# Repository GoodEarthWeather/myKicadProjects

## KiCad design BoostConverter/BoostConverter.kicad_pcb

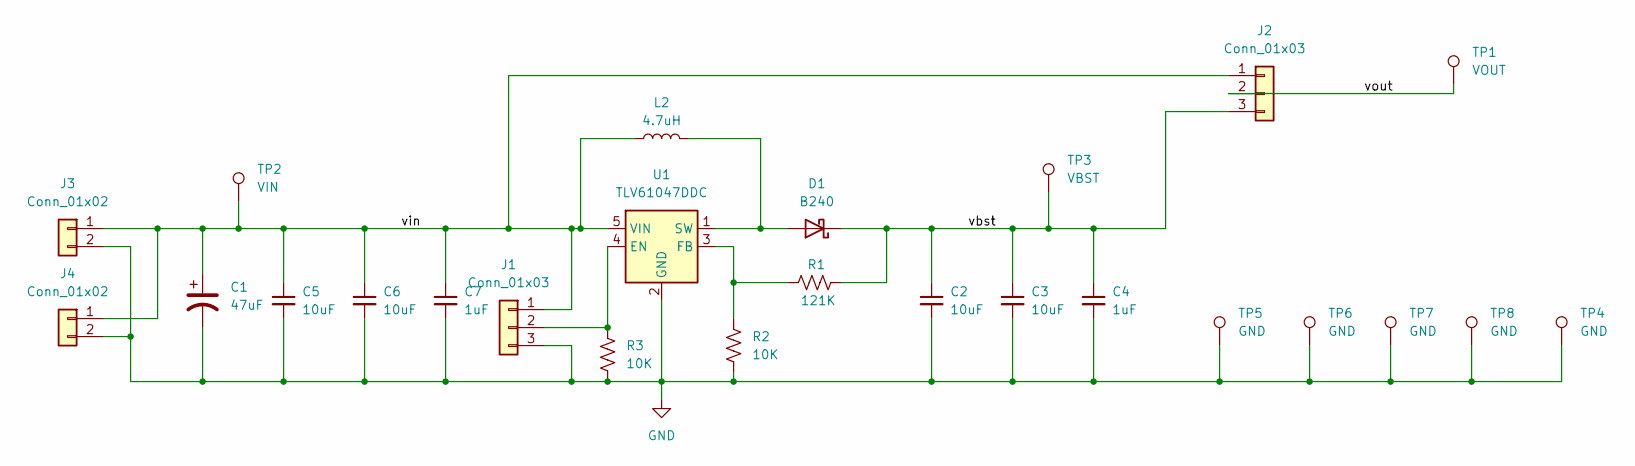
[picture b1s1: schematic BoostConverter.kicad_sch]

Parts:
C1: 47uF; CP_Elec_6.3x5.8; MouserPN 667-EEE-FK1V470P
C2, C3, C5, C6: 10uF; C_1206_3216Metric_Pad1.33x1.80mm_HandSolder; MouserPN 810-CGA5L1X7R1H106K1
C4, C7: 1uF; C_0603_1608Metric_Pad1.08x0.95mm_HandSolder; MouserPN 963-BASG168AB7105KT
D1: B240; D_SMB; MouserPN 625-B240A-E3
J1, J2: Conn_01x03; PinHeader_1x03_P2.54mm_Vertical
J3, J4: Conn_01x02; PinHeader_1x02_P2.54mm_Vertical
L2: 4.7uH; L_Coilcraft_XAL4030-XXX
R1: 121K; R_0603_1608Metric_Pad0.98x0.95mm_HandSolder
R2, R3: 10K; R_0603_1608Metric_Pad0.98x0.95mm_HandSolder
TP1: VOUT; TestPoint_Keystone_5000-5004_Miniature; MouserPN 534-5003
TP2: VIN; TestPoint_Keystone_5000-5004_Miniature; MouserPN 534-5003
TP3: VBST; TestPoint_Keystone_5000-5004_Miniature; MouserPN 534-5003
TP4, TP5, TP6, TP7, TP8: GND; TestPoint_Keystone_5000-5004_Miniature; MouserPN 534-5003
U1: TLV61047DDC; SOT-23-5

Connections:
/vbst: C2.1, C3.1, C4.1, D1.1 (K), J2.3, R1.2, TP3.1
/vin: C1.1, C5.1, C6.1, C7.1, J1.1, J2.1, J3.1, J4.1, L2.1, TP2.1, U1.5 (VIN)
/vout: J2.2, TP1.1
GND: C1.2, C2.2, C3.2, C4.2, C5.2, C6.2, C7.2, J1.3, J3.2, J4.2, R2.2, R3.2, TP4.1, TP5.1, TP6.1, TP7.1, TP8.1, U1.2 (GND)
unnamed: D1.2 (A), L2.2, U1.1 (SW)
unnamed: J1.2, R3.1, U1.4 (EN)
unnamed: R1.1, R2.1, U1.3 (FB)

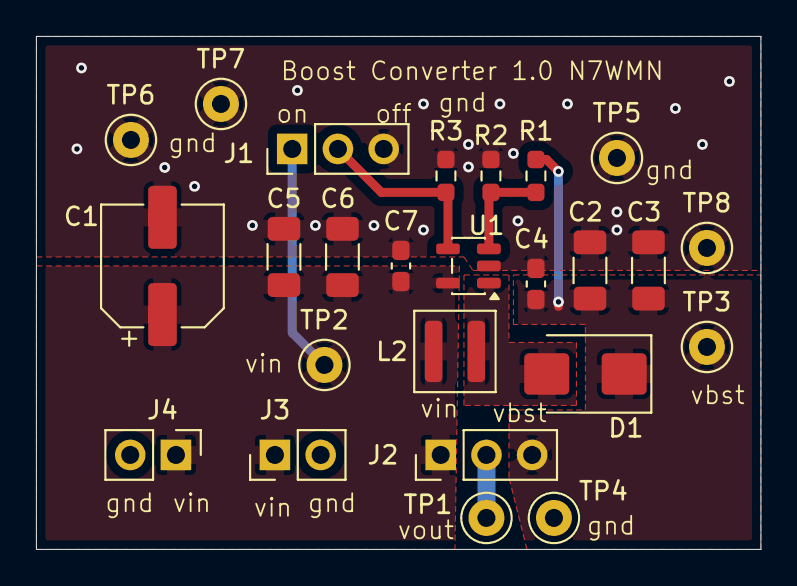
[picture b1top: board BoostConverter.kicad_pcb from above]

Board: 2 copper layers, 40.2 x 28.5 mm, 25 parts (0 on the bottom side), 7 nets.

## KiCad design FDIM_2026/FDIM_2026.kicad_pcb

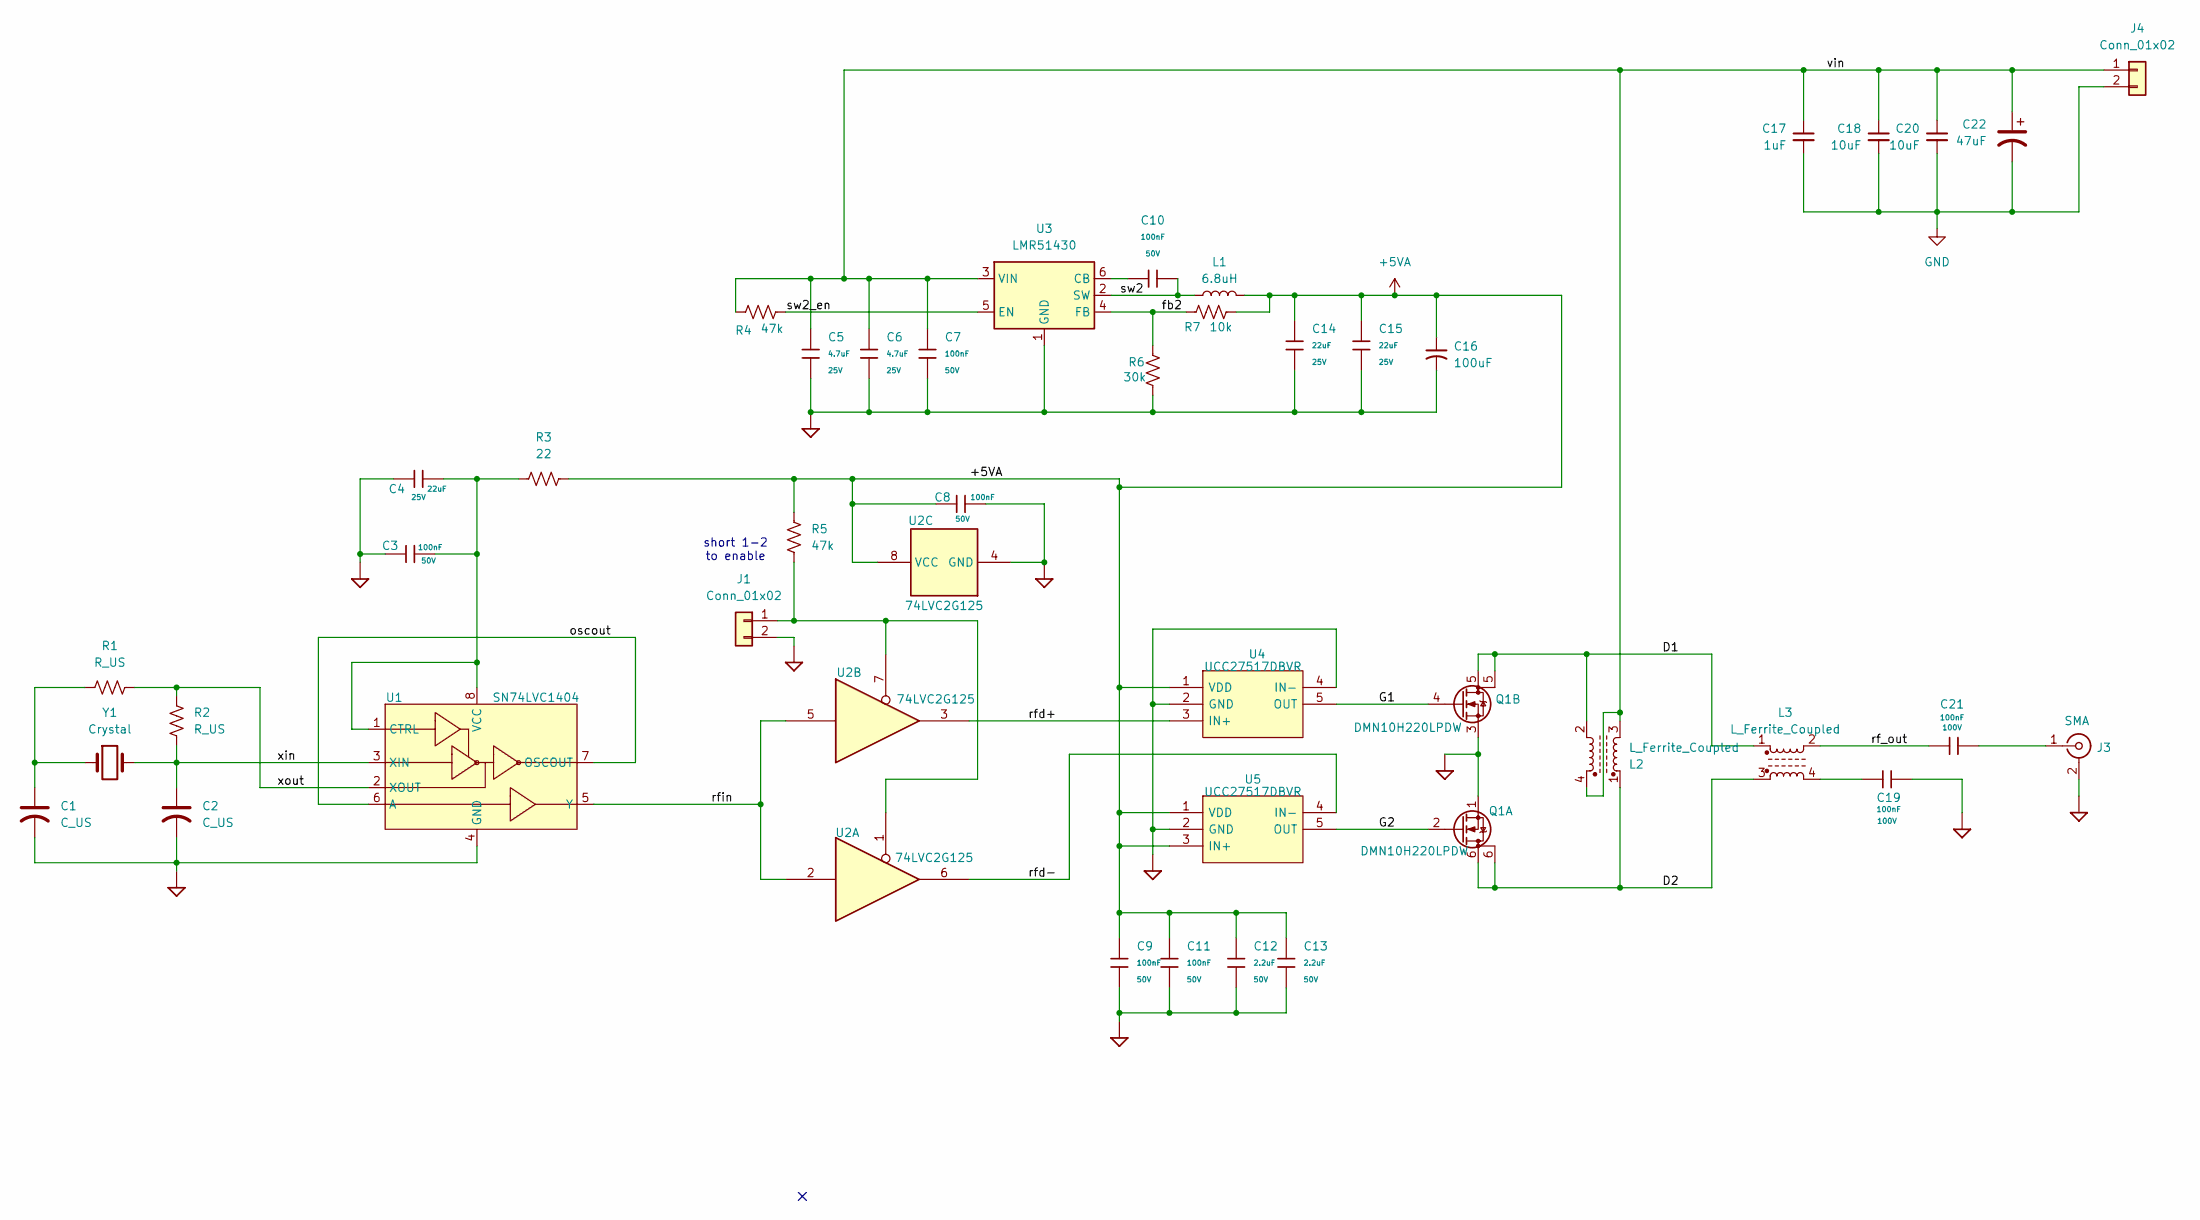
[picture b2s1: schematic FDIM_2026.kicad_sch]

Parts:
C1, C2: C_US; C_0603_1608Metric_Pad1.08x0.95mm_HandSolder
C3, C7, C8, C9, C10, C11: 100nF; C_0603; Voltage Rated 50V; Tolerance ±10%; Part CC0603KRX7R9BB104; LCSC C14663
C4, C14, C15: 22uF; C_0805; Voltage Rated 25V; Tolerance ±20%; Part CL21A226MAQNNNE; LCSC C45783
C5, C6: 4.7uF; C_0805; Voltage Rated 25V; Tolerance ±10%; Part CL21A475KAQNNNE; LCSC C1779
C12, C13: 2.2uF; C_0805; Voltage Rated 50V; Tolerance ±10%; Part CL21A225KBQNNNE; LCSC C377773
C16: 100uF; C_Elec_6.3x5.8; MouserPN 667-EEE-FT1V101AP
C17: 1uF; C_0603; MouserPN 963-BASG168AB7105KT
C18, C20: 10uF; C_1206; MouserPN 810-CGA5L1X7R1H106K1
C19, C21: 100nF; C_0805; Voltage Rated 100V; Tolerance ±10%; Part CL21B104KCFNNNE; LCSC C28233
C22: 47uF; CP_Elec_6.3x5.8; MouserPN 667-EEE-FK1V470P
J1, J4: Conn_01x02; PinHeader_1x02_P2.54mm_Vertical
J3: SMA; SMA_Molex_73251-1153_EdgeMount_Horizontal
L1: 6.8uH; L_TechFuse_SL0624; MouserPN 871-B82472G4682M
L2, L3: L_Ferrite_Coupled; Transformer_Toroid_Horizontal_D14.0mm_Amidon-T50
Q1: DMN10H220LPDW; DMN10H220LPDW13; MouserPN 621-DMN10H220LPDW-13
R1, R2: R_US; R_0603_1608Metric_Pad0.98x0.95mm_HandSolder
R3: 22; R_0603_1608Metric_Pad0.98x0.95mm_HandSolder
R4, R5: 47k; R_0603_1608Metric_Pad0.98x0.95mm_HandSolder
R6: 30k; R_0603_1608Metric_Pad0.98x0.95mm_HandSolder
R7: 10k; R_0603_1608Metric_Pad0.98x0.95mm_HandSolder
U1: SN74LVC1404; TSSOP-8_3x3mm_P0.65mm; MouserPN 595-SN74LVC1404DCTR
U2: 74LVC2G125; SSOP-8_2.95x2.8mm_P0.65mm; MouserPN 595-74LVC2G125DCTRE4
U3: LMR51430; SOT-23-6; LCSC C5185863
U4, U5: UCC27517DBVR; SOT-23-5_HandSoldering; Mouser Part Number 595-UCC27517DBVR
Y1: Crystal; Crystal_HC49-U_Vertical; MouserPN 449-LFXTAL011525BULK

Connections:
+5VA: C8.1, C9.1, C11.1, C12.1, C13.1, C14.1, C15.1, C16.1, L1.2, R3.1, R5.2, R7.1, U2.8 (VCC), U4.1 (VDD), U5.1 (VDD), U5.3 (IN+)
/D1: L2.2, L3.1, Q1.5 (D)
/D2: L2.1, L3.3, Q1.6 (D)
/G1: Q1.4 (G), U4.5 (OUT)
/G2: Q1.2 (G), U5.5 (OUT)
/fb2: R6.2, R7.2, U3.4 (FB)
/oscout: U1.6 (A), U1.7 (OSCOUT)
/rf_out: C21.1, L3.2
/rfd+: U2.3, U4.3 (IN+)
/rfd-: U2.6, U5.4 (IN-)
/rfin: U1.5 (Y), U2.2, U2.5
/sw2: C10.2, L1.1, U3.2 (SW)
/sw2_en: R4.1, U3.5 (EN)
/vin: C5.1, C6.1, C7.1, C17.1, C18.1, C20.1, C22.1, J4.1, L2.3, L2.4, R4.2, U3.3 (VIN)
/xin: C2.1, R2.1, U1.3 (XIN), Y1.2
/xout: R1.2, R2.2, U1.2 (XOUT)
GND: C1.2, C2.2, C3.1, C4.1, C5.2, C6.2, C7.2, C8.2, C9.2, C11.2, C12.2, C13.2, C14.2, C15.2, C16.2, C17.2, C18.2, C19.2, C20.2, C22.2, J1.2, J3.2 (Ext), J4.2, Q1.1 (S), Q1.3 (S), R6.1, U1.4 (GND), U2.4 (GND), U3.1 (GND), U4.2 (GND), U4.4 (IN-), U5.2 (GND)
unnamed: C1.1, R1.1, Y1.1
unnamed: C19.1, L3.4
unnamed: J1.1, R5.1, U2.1, U2.7
unnamed: C21.2, J3.1 (In)
unnamed: C3.2, C4.2, R3.2, U1.1 (CTRL), U1.8 (VCC)
unnamed: C10.1, U3.6 (CB)

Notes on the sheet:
short 1-2 to enable

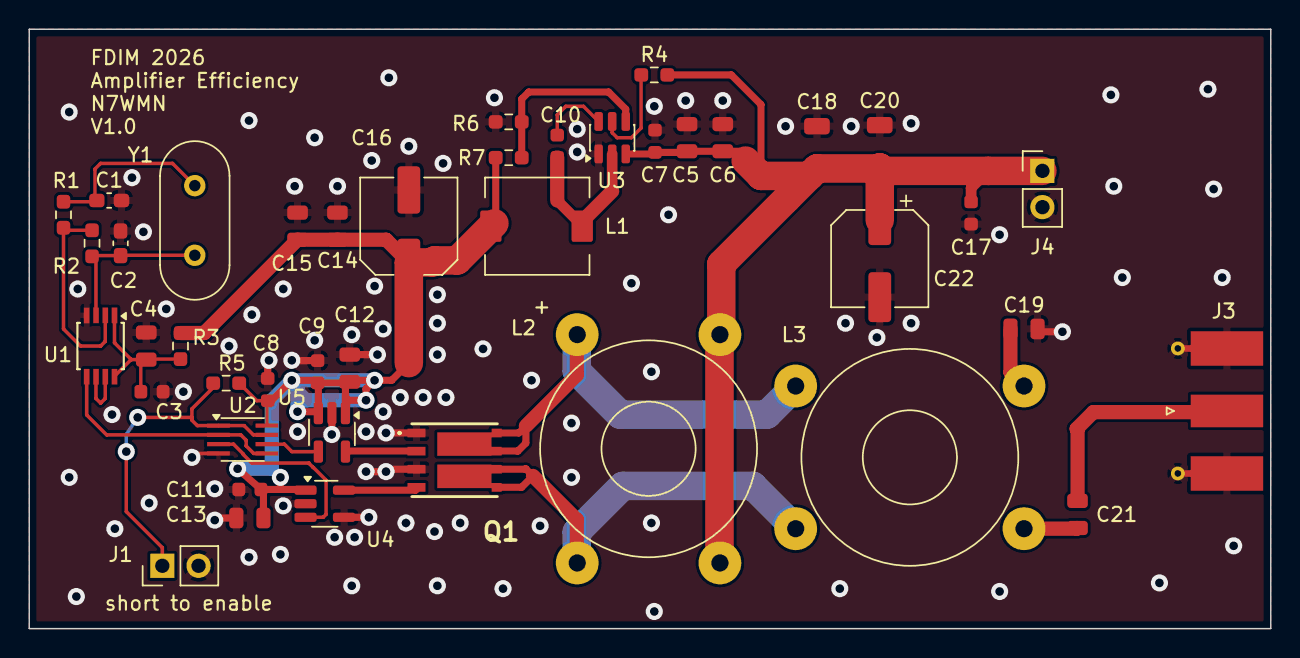
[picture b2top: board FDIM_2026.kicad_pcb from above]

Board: 2 copper layers, 87.0 x 42.0 mm, 42 parts (0 on the bottom side), 23 nets.

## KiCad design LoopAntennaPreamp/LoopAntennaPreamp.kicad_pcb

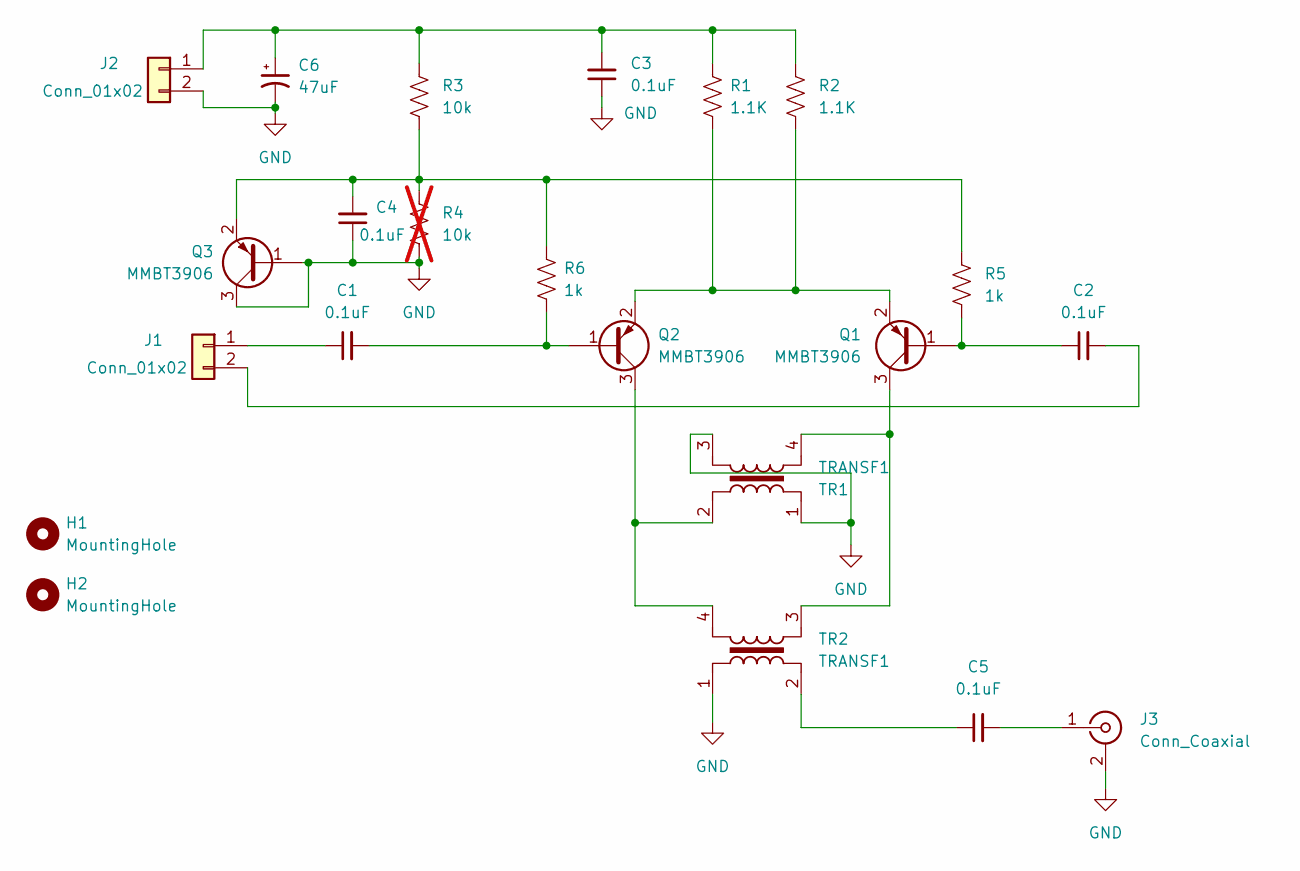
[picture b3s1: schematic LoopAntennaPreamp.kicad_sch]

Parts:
C1, C2, C3, C4, C5: 0.1uF; C_0603_1608Metric_Pad1.08x0.95mm_HandSolder
C6: 47uF; CP_Radial_D5.0mm_P2.50mm
H1, H2: MountingHole; MountingHole_3.2mm_M3_DIN965
J1, J2: Conn_01x02; PinHeader_1x02_P2.54mm_Vertical
J3: Conn_Coaxial; SMA_Amphenol_132289_EdgeMount
Q1, Q2, Q3: MMBT3906; SOT-23_Handsoldering
R1, R2: 1.1K; R_0603_1608Metric_Pad0.98x0.95mm_HandSolder
R3: 10k; R_0603_1608Metric_Pad0.98x0.95mm_HandSolder
R4: 10k; R_0603_1608Metric_Pad0.98x0.95mm_HandSolder; not fitted
R5, R6: 1k; R_0603_1608Metric_Pad0.98x0.95mm_HandSolder
TR1, TR2: TRANSF1; Transformer_Toroid_Horizontal_D10.5mm_Amidon-T37

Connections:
GND: C3.1, C4.1, C6.2, J2.2, J3.2 (Ext), Q3.1 (B), Q3.3 (C), R4.2, TR1.1, TR1.3, TR2.1
unnamed: C5.1, TR2.2
unnamed: C1.1, J1.1
unnamed: C2.2, J1.2
unnamed: C3.2, C6.1, J2.1, R1.1, R2.1, R3.1
unnamed: C5.2, J3.1 (In)
unnamed: C2.1, Q1.1 (B), R5.1
unnamed: Q1.3 (C), TR1.4, TR2.3
unnamed: Q1.2 (E), Q2.2 (E), R1.2, R2.2
unnamed: C1.2, Q2.1 (B), R6.1
unnamed: Q2.3 (C), TR1.2, TR2.4
unnamed: C4.2, Q3.2 (E), R3.2, R4.1, R5.2, R6.2

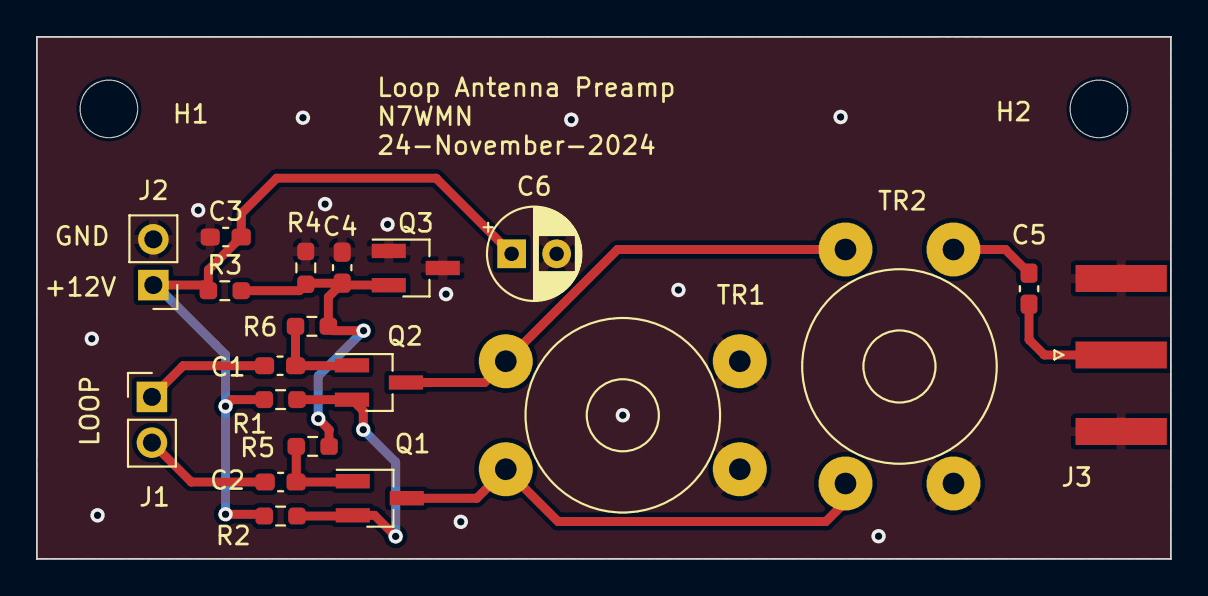
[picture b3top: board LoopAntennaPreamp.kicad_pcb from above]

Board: 2 copper layers, 63.0 x 29.0 mm, 22 parts (0 on the bottom side), 12 nets.

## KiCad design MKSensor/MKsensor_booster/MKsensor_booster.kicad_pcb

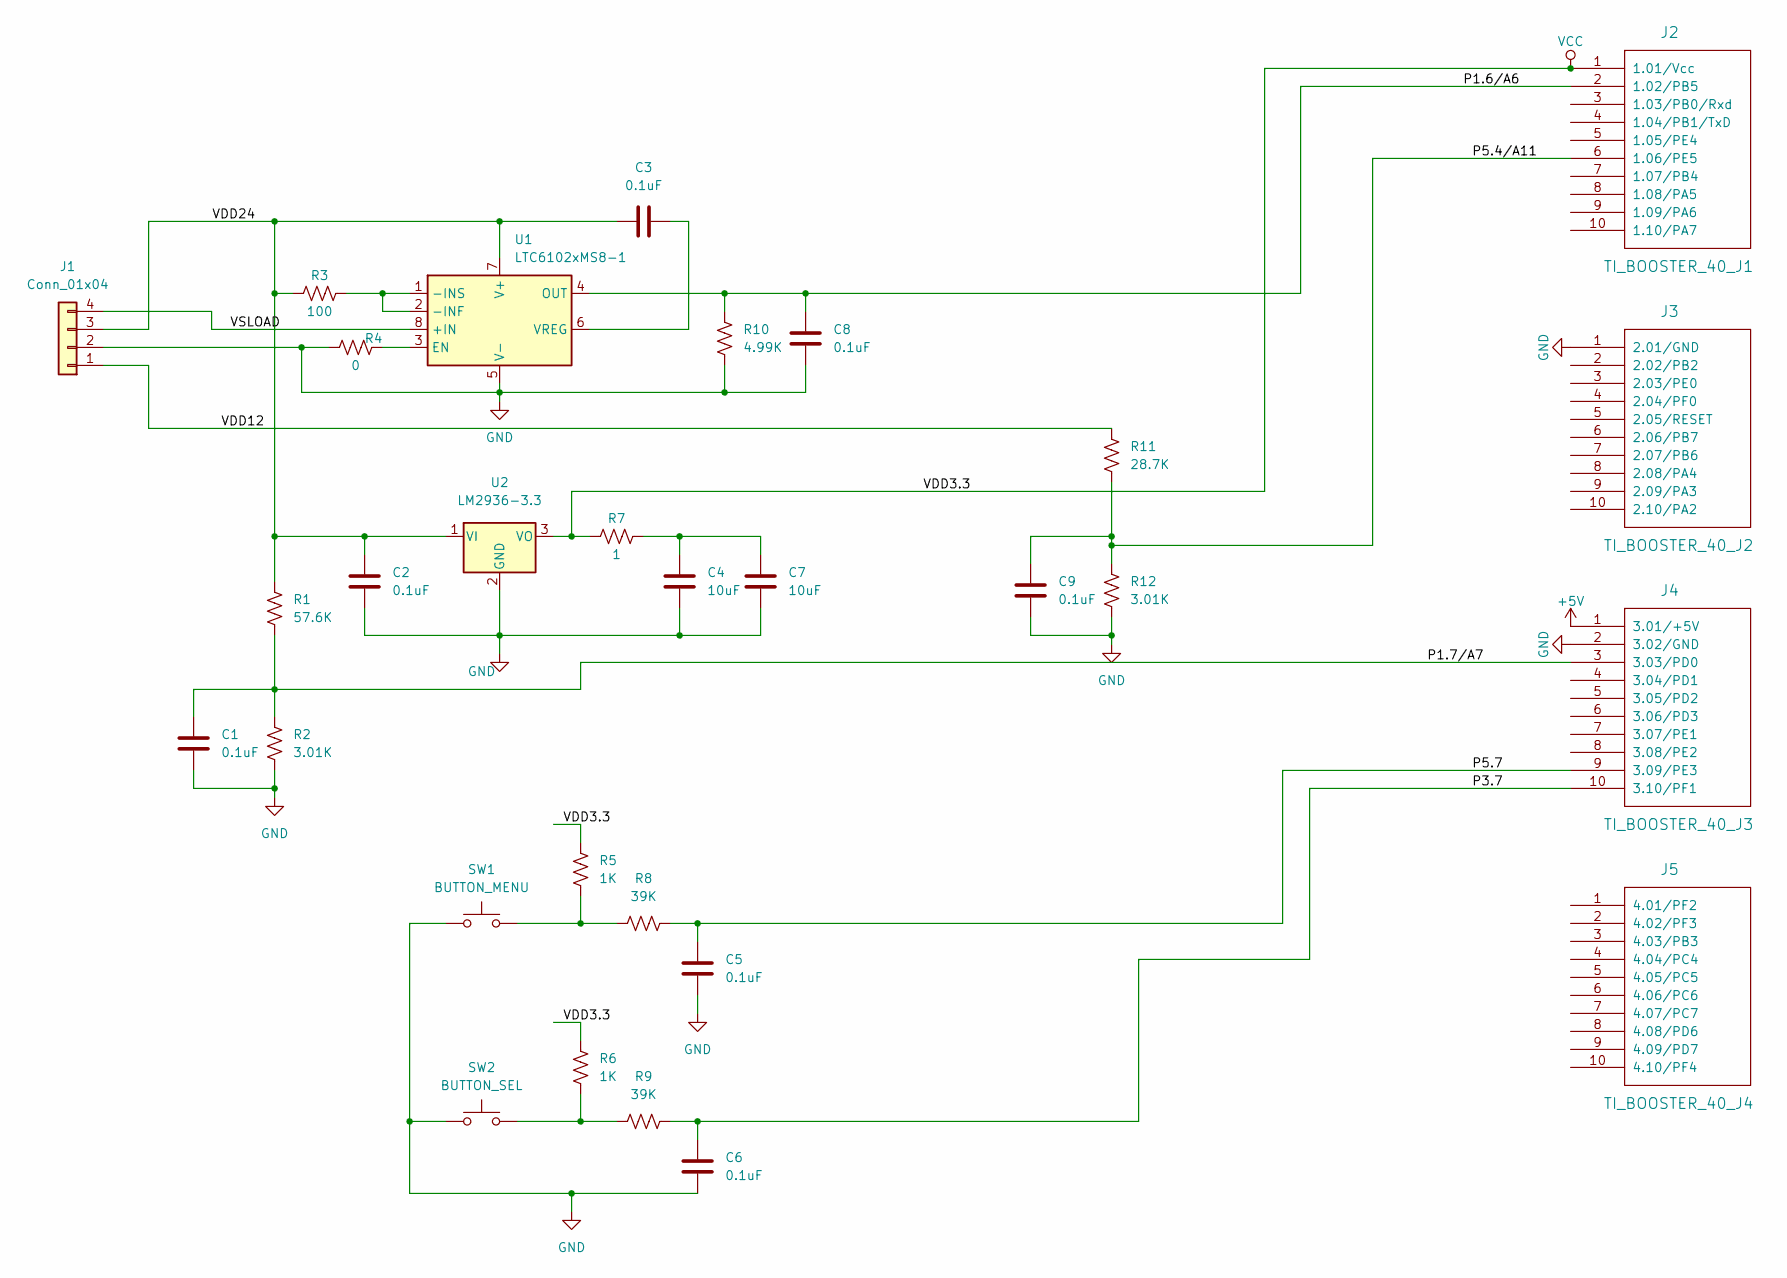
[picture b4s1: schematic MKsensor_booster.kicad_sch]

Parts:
C1, C2, C3, C5, C6, C8, C9: 0.1uF; C_0603_1608Metric_Pad1.08x0.95mm_HandSolder
C4, C7: 10uF; C_0805_2012Metric_Pad1.18x1.45mm_HandSolder
J1: Conn_01x04; PhoenixContact_MCV_1,5_4-G-3.81_1x04_P3.81mm_Vertical
J2: TI_BOOSTER_40_J1; PinHeader_1x10_P2.54mm_Vertical
J3: TI_BOOSTER_40_J2; PinHeader_1x10_P2.54mm_Vertical
J4: TI_BOOSTER_40_J3; PinHeader_1x10_P2.54mm_Vertical
J5: TI_BOOSTER_40_J4; PinHeader_1x10_P2.54mm_Vertical
R1: 57.6K; R_0603_1608Metric_Pad0.98x0.95mm_HandSolder
R2, R12: 3.01K; R_0603_1608Metric_Pad0.98x0.95mm_HandSolder
R3: 100; R_0603_1608Metric_Pad0.98x0.95mm_HandSolder
R4: 0; R_0603_1608Metric_Pad0.98x0.95mm_HandSolder
R5, R6: 1K; R_0603_1608Metric_Pad0.98x0.95mm_HandSolder
R7: 1; R_0603_1608Metric_Pad0.98x0.95mm_HandSolder
R8, R9: 39K; R_0603_1608Metric_Pad0.98x0.95mm_HandSolder
R10: 4.99K; R_0603_1608Metric_Pad0.98x0.95mm_HandSolder
R11: 28.7K; R_0603_1608Metric_Pad0.98x0.95mm_HandSolder
SW1: BUTTON_MENU; SW_SPST_EVQQ2
SW2: BUTTON_SEL; SW_SPST_EVQQ2
U1: LTC6102xMS8-1; MSOP-8_3x3mm_P0.65mm
U2: LM2936-3.3; SOT-223

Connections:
+5V: J4.1 (3.01/+5V)
/P1.6/A6: C8.2, J2.2 (1.02/PB5), R10.1, U1.4 (OUT)
/P1.7/A7: C1.2, J4.3 (3.03/PD0), R1.2, R2.1
/P3.7: C6.2, J4.10 (3.10/PF1), R9.2
/P5.4/A11: C9.2, J2.6 (1.06/PE5), R11.2, R12.1
/P5.7: C5.2, J4.9 (3.09/PE3), R8.2
/VDD12: J1.1, R11.1
/VDD24: C2.2, C3.1, J1.3, R1.1, R3.1, U1.7 (V+), U2.1 (VI)
/VSLOAD: J1.4, U1.8 (+IN)
GND: C1.1, C2.1, C4.1, C5.1, C6.1, C7.1, C8.1, C9.1, J1.2, J3.1 (2.01/GND), J4.2 (3.02/GND), R2.2, R4.1, R10.2, R12.2, SW1.1, SW2.1, U1.5 (V-), U2.2 (GND)
unnamed: C3.2, U1.6 (VREG)
unnamed: C4.2, C7.2, R7.2
unnamed: R3.2, U1.1 (-INS), U1.2 (-INF)
unnamed: R4.2, U1.3 (EN)
unnamed: R5.1, R8.1, SW1.2
unnamed: R6.1, R9.1, SW2.2
VCC: J2.1 (1.01/Vcc), R5.2, R6.2, R7.1, U2.3 (VO)

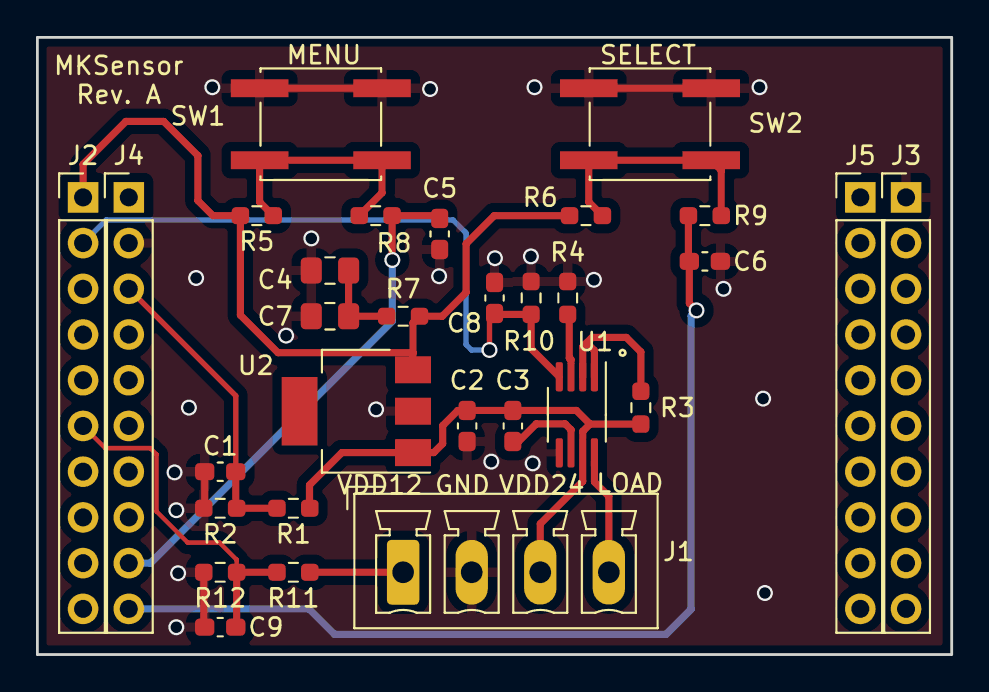
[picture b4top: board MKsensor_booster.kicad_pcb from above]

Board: 2 copper layers, 50.8 x 34.3 mm, 30 parts (0 on the bottom side), 16 nets.

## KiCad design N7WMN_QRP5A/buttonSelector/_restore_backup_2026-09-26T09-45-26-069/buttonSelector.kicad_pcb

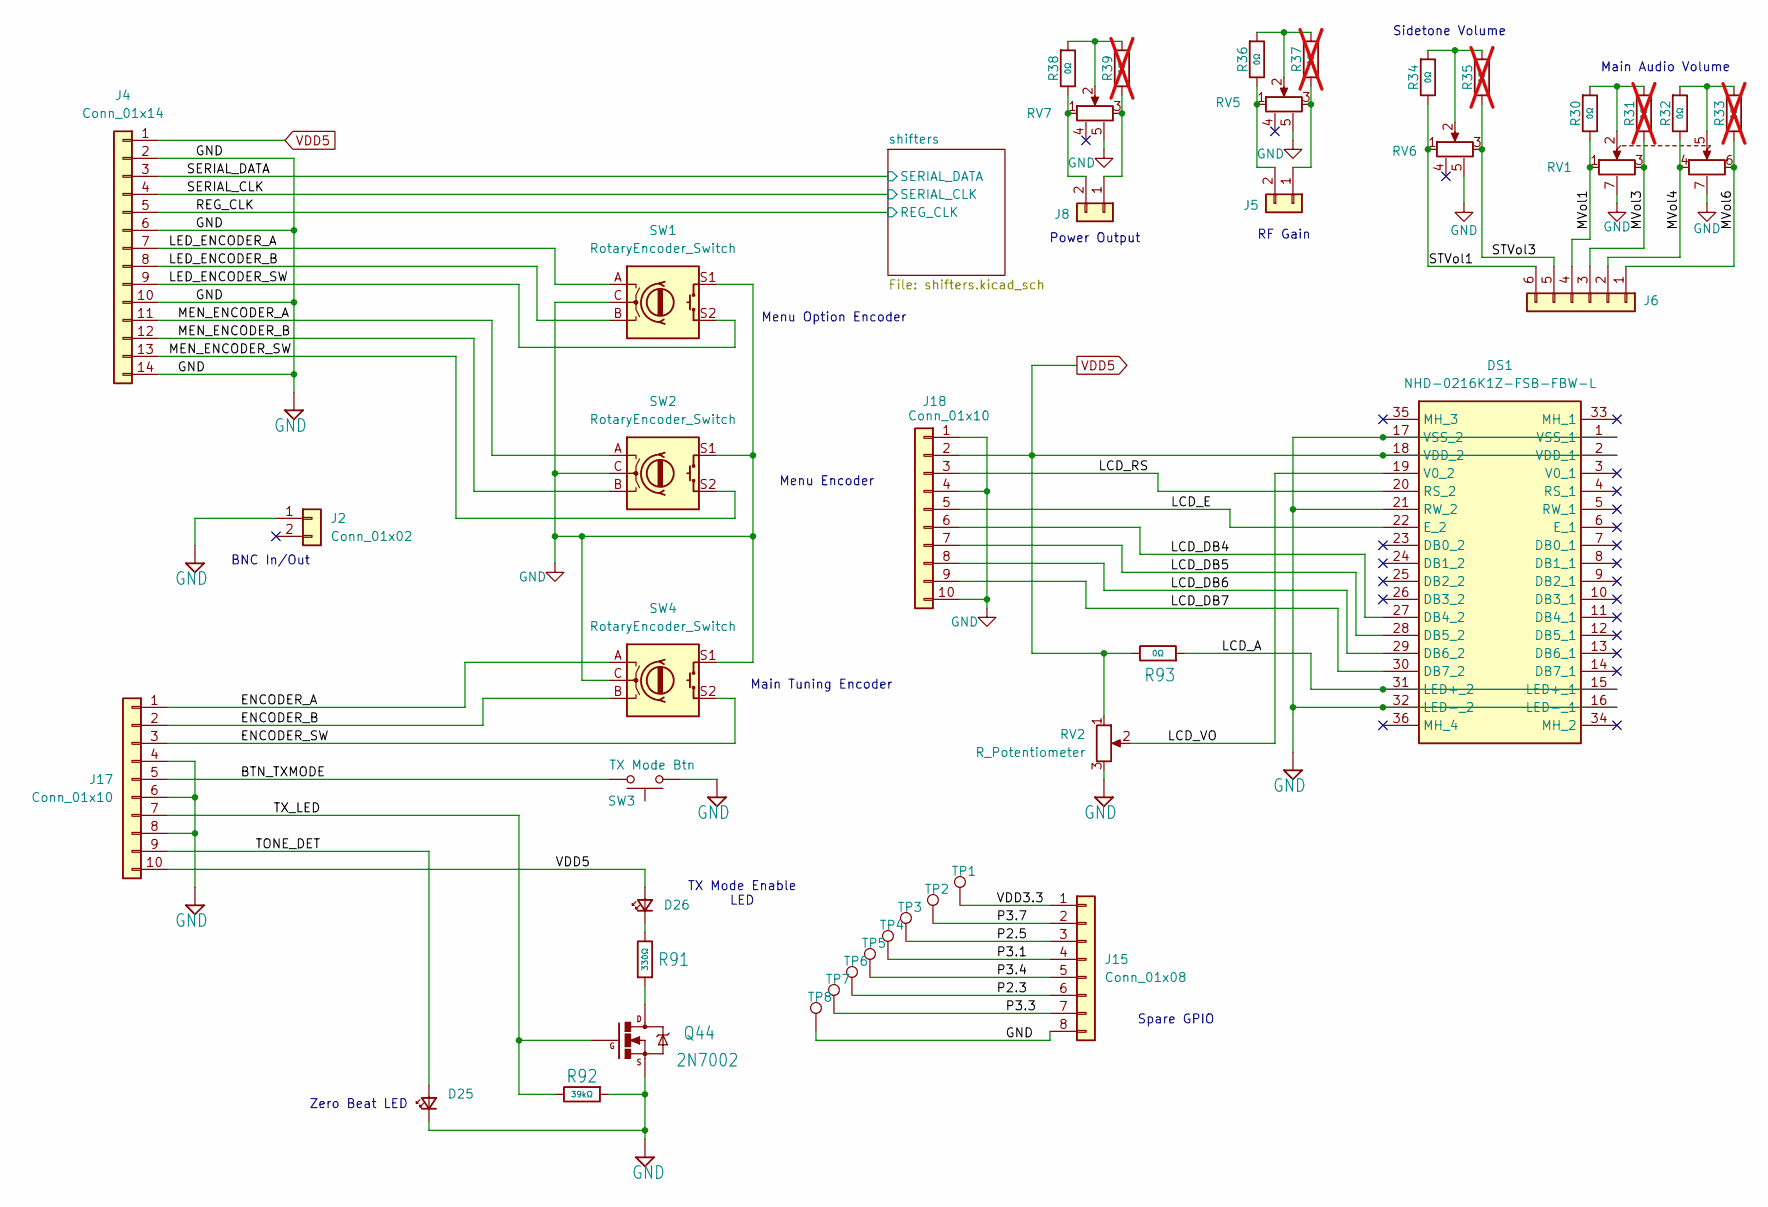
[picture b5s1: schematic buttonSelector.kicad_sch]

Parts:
D25, D26: LED_Small; LED_D5.0mm; MouserPN 606-CMD333URC2
DS1: NHD-0216K1Z-FSB-FBW-L; NHD0216K1ZFSBFBWL; Mouser Part Number 763-0216K1Z-FSB-FBW
J2, J5, J8: Conn_01x02; PinHeader_1x02_P2.54mm_Vertical
J4: Conn_01x14; PinHeader_1x14_P2.54mm_Vertical
J6: Conn_01x06; PinHeader_1x06_P2.54mm_Vertical
J15: Conn_01x08; PinHeader_1x08_P2.54mm_Vertical
J17, J18: Conn_01x10; PinHeader_1x10_P2.54mm_Vertical
Q44: 2N7002; SOT-23; JLCPCB C65189
R30, R32, R34, R36, R38, R93: 0Ω; R_0603; Overload Voltage (Max) 75V; Tolerance ±1%; Part 0603WAF0000T5E; LCSC C21189
R31, R33, R35, R37, R39: 0Ω; R_0603; Overload Voltage (Max) 75V; Tolerance ±1%; Part 0603WAF0000T5E; LCSC C21189; not fitted
R91: 330Ω; R_0603; Overload Voltage (Max) 75V; Tolerance ±1%; Part 0603WAF3300T5E; LCSC C23138
R92: 39kΩ; R_0603; Overload Voltage (Max) 75V; Tolerance ±1%; Part 0603WAF3902T5E; LCSC C23153
RV1: R_Potentiometer_Dual; PVT112-4_Potentiometer; Mouser Part Number 652-PTV112-4420AA103
RV2: R_Potentiometer; Potentiometer_Bourns_3386C_Horizontal
RV5: R_Potentiometer_PVT111; PVT111-4_Potentiometer; Mouser Part Number 652-PTV111-4420AB503
RV6: R_Potentiometer_PVT111; PVT111-4_Potentiometer; Mouser Part Number 652-PTV111-4420AA502
RV7: R_Potentiometer_PVT111; PVT111-4_Potentiometer; Mouser Part Number 652-PTV111-4420AB502
SW1, SW2: RotaryEncoder_Switch; RotaryEncoder_Alps_EC11E-Switch_Vertical_H20mm; Mouser Part Number 652-PEC11R-4220F-S24
SW3: TX Mode Btn; SW_PUSH-12mm
SW4: RotaryEncoder_Switch; RotaryEncoder_Alps_EC11E-Switch_Vertical_H20mm; Mouser Part Number 652-PEC11R-4020F-S24
TP1, TP2, TP3, TP4, TP5, TP6, TP7, TP8: TestPoint; TestPoint_Loop_D2.50mm_Drill1.0mm

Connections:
/BTN_TXMODE: J17.5, SW3.2
/ENCODER_A: J17.1, SW4.A
/ENCODER_B: J17.2, SW4.B
/ENCODER_SW: J17.3, SW4.S2
/LCD_A: DS1.15 (LED+_1), DS1.31 (LED+_2), R93.1
/LCD_DB4: DS1.27 (DB4_2), J18.6
/LCD_DB5: DS1.28 (DB5_2), J18.7
/LCD_DB6: DS1.29 (DB6_2), J18.8
/LCD_DB7: DS1.30 (DB7_2), J18.9
/LCD_E: DS1.22 (E_2), J18.5
/LCD_RS: DS1.20 (RS_2), J18.3
/LCD_VO: DS1.19 (V0_2), RV2.2
/LED_ENCODER_A: J4.7, SW1.A
/LED_ENCODER_B: J4.8, SW1.B
/LED_ENCODER_SW: J4.9, SW1.S2
/MEN_ENCODER_A: J4.11, SW2.A
/MEN_ENCODER_B: J4.12, SW2.B
/MEN_ENCODER_SW: J4.13, SW2.S2
/MVol1: J6.4, R30.2, RV1.1
/MVol3: J6.3, R31.2, RV1.3
/MVol4: J6.2, R32.2, RV1.4
/MVol6: J6.1, R33.2, RV1.6
/P2.3: J15.6, TP6.1 (1_1)
/P2.5: J15.3, TP3.1 (1_1)
/P3.1: J15.4, TP4.1 (1_1)
/P3.3: J15.7, TP7.1 (1_1)
/P3.4: J15.5, TP5.1 (1_1)
/P3.7: J15.2, TP2.1 (1_1)
/REG_CLK: J4.5; also elsewhere on the board
/SERIAL_CLK: J4.4; also elsewhere on the board
/SERIAL_DATA: J4.3; also elsewhere on the board
/STVol1: J6.6, R34.2, RV6.1
/STVol3: J6.5, R35.2, RV6.3
/TONE_DET: D25.2 (A), J17.9
/TX_LED: J17.7, Q44.1 (G), R92.2
/VDD3.3: J15.1, TP1.1 (1_1)
GND: D25.1 (K), DS1.1 (VSS_1), DS1.16 (LED-_1), DS1.17 (VSS_2), DS1.21 (RW_2), DS1.32 (LED-_2), J2.1 (Pin_1_1), J4.2, J4.6, J4.10, J4.14, J15.8, J17.4, J17.6, J17.8, J18.1, J18.4, J18.10, Q44.2 (S), R92.1, RV1.7 (NC), RV2.3, RV5.5 (gnd), RV6.5 (gnd), RV7.5 (gnd), SW1.C, SW1.S1, SW2.C, SW2.S1, SW3.1, SW4.C, SW4.S1, TP8.1 (1_1); also elsewhere on the board
unnamed: D26.1 (K), R91.2
unnamed: J5.1, R37.2, RV5.3
unnamed: J5.2, R36.2, RV5.1
unnamed: J8.1, R39.2, RV7.3
unnamed: J8.2, R38.2, RV7.1
unnamed: Q44.3 (D), R91.1
unnamed: R30.1, R31.1, RV1.2
unnamed: R32.1, R33.1, RV1.5
unnamed: R34.1, R35.1, RV6.2
unnamed: R36.1, R37.1, RV5.2
unnamed: R38.1, R39.1, RV7.2
VDD5: D26.2 (A), DS1.2 (VDD_1), DS1.18 (VDD_2), J4.1, J17.10, J18.2, R93.2, RV2.1; also elsewhere on the board

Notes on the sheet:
Main Tuning Encoder
Menu Encoder
Menu Option Encoder
BNC In/Out
Sidetone Volume
RF Gain
Main Audio Volume
TX Mode Enable LED
Power Output
Spare GPIO
Zero Beat LED
